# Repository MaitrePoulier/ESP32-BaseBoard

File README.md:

The goals of this BaseBoard:
* Support Bluetooth legacy for receiving audio from an external audio source
* Support 2x 18650 LiFePo4 cell that can be charged with the USB connector
* Low noise +/- 12.4V going to the mezzanine to powered Audio op-amp
* I2S port going to the mezz
* Support of the MHS 4.0 screen (ST7796S) with touch (XPT2046)
* can be placed inside an Pelican 1040 Micro Case

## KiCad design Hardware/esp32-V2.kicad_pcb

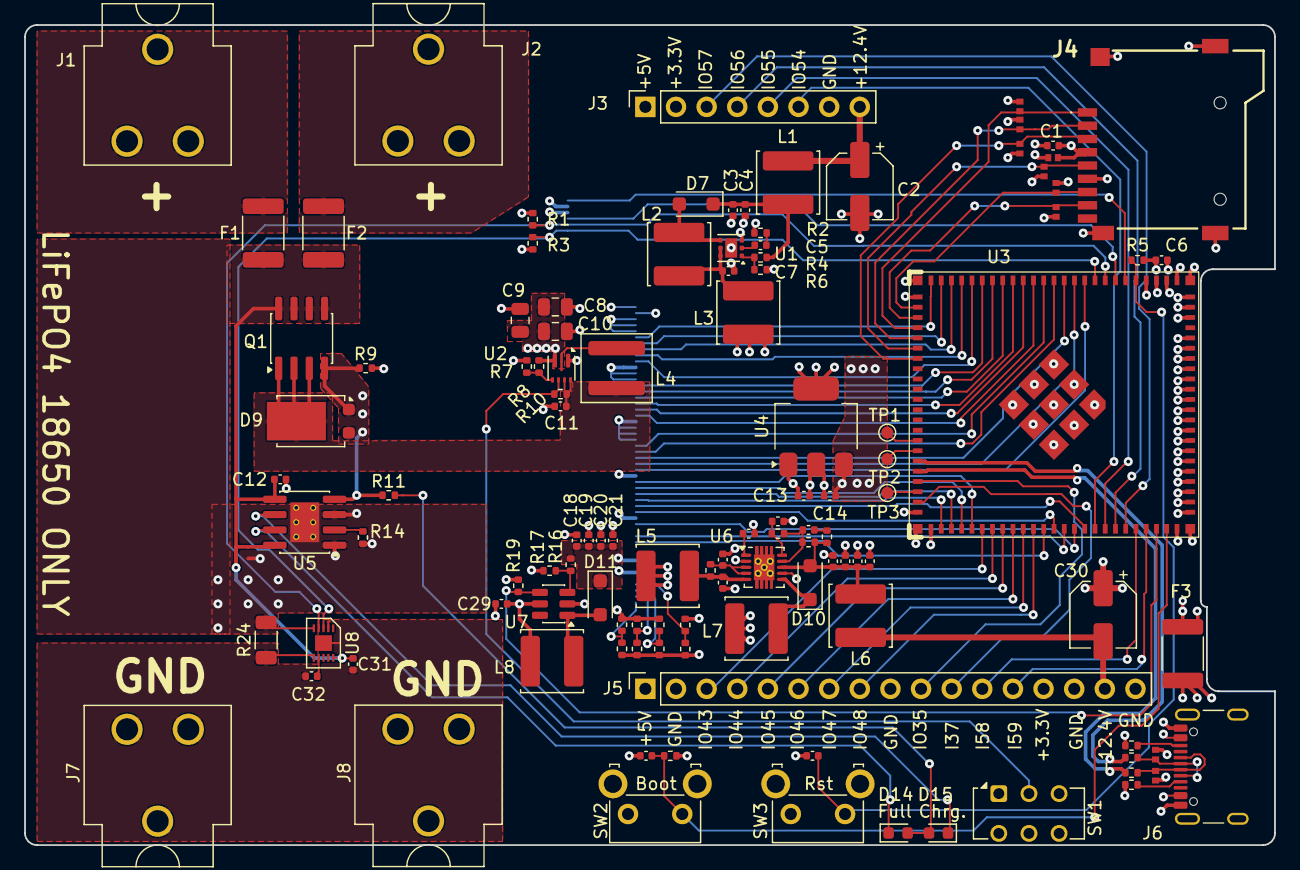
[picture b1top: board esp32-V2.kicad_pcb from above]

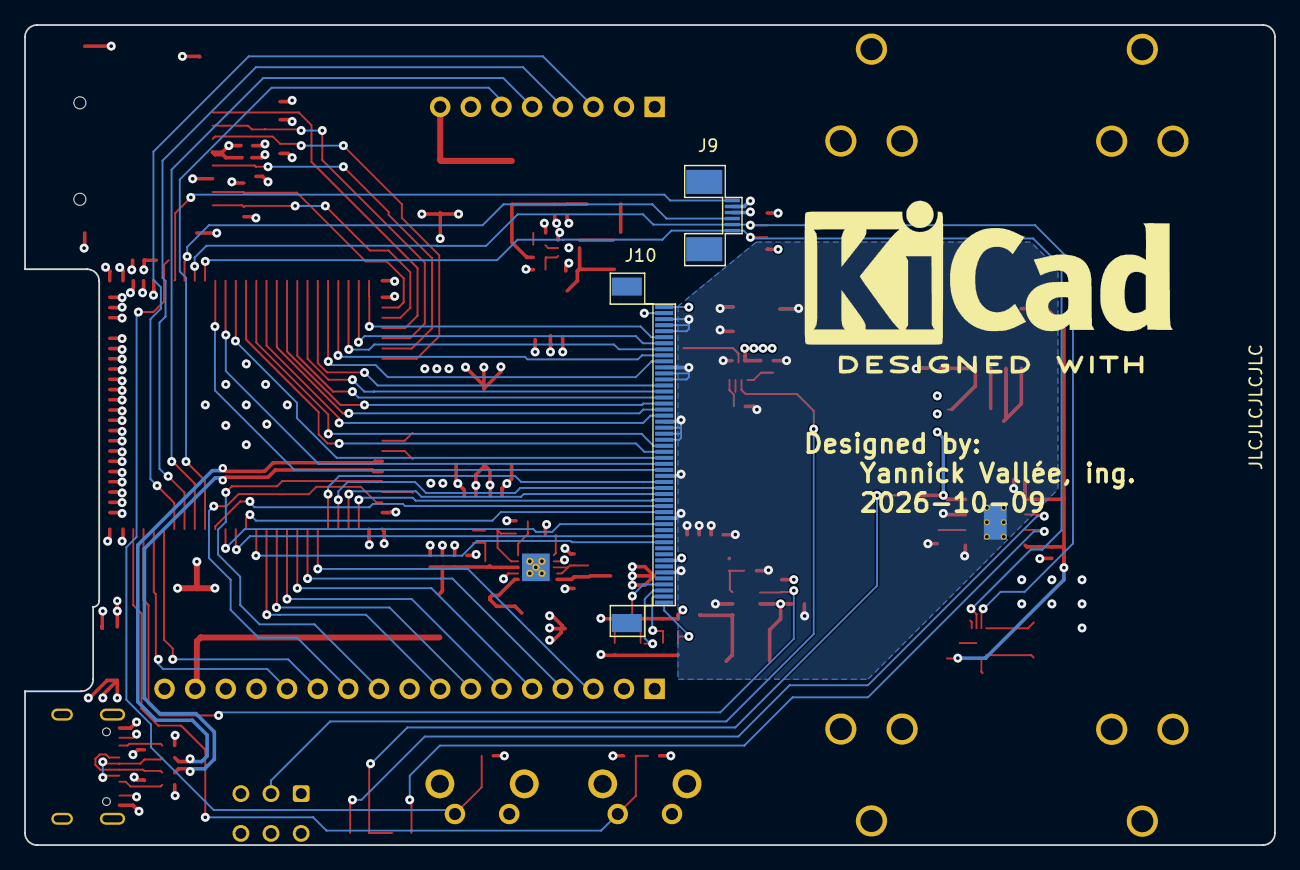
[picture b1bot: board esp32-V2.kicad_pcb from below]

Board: 4 copper layers, 103.7 x 68.0 mm, 118 parts (2 on the bottom side), 103 nets.

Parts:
C1, C6, C7, C11, C12, C13, C14, C28, C29: 10uF; C_0402_1005Metric
C2, C30: 22uF; CP_Elec_5x5.9
C3, C18, C19, C20, C21, C24, C25, C26, C27: 4.7uF; C_0402_1005Metric
C4, C5, C17: 4.7nF; C_0402_1005Metric
C8, C9, C10: 22uF; C_0805_2012Metric
C15, C23: 220nF; C_0402_1005Metric
C16: 10pF; C_0402_1005Metric
C31, C32: 470nF; C_0402_1005Metric
C33, C34: 1nF; C_0402_1005Metric
D1, D2, D3, D4, D5, D6, D8, D12, D13: BSDFN2C031U; D_DFN1006-2L
D7, D10, D11: Diode-DK24; D_SOD-123F
D9: Diode-PDS760; TO-277B
D14: Blue 2.9V; LED_0603_1608Metric
D15: Green, 3.2V; LED_0603_1608Metric
F1, F2, F3: BSMD1812-300-16V; Fuse_1812_4532Metric_Pad1.30x3.40mm_HandSolder
J1, J2, J7, J8: Conn_01x01_Socket; BatteryClip_Keystone_54_D16-19mm
J3: Conn_01x08_F_Header; PinSocket_1x08_P2.54mm_Vertical
J4: MSD-4-A; MSD4A
J5: PM254-1-17-Z-8.5; PinSocket_1x17_P2.54mm_Vertical
J6: USB_C_Receptacle-16p; USB_C_Receptacle_GCT_USB4105-xx-A_16P_TopMnt_Horizontal
J9: KH-FG0.5-H2.0-6PIN; ER-CON06HT-1
J10: HC-FPC-0.5-50P-FHH20
L1, L3, L5, L6: 2.9Ohms @ 1Mhz; L_Chilisin_BWVS00505030
L2, L7, L8: 10uH; L_Chilisin_BWVS00505030
L4: 1uH; L_Coilcraft_XAL5030-XXX
NT1: NetTie_2; NetTie-2_SMD_Pad0.16mm
Q1: DMP3015LSS-13; SOIC-8_3.9x4.9mm_P1.27mm
R1, R3, R5, R7, R9, R10, R13, R19, R20, R21, R22, R23, R25, R26, R27, R28, R30: 100k; R_0402_1005Metric
R2, R6: 10k; R_0402_1005Metric
R4: 91k; R_0402_1005Metric
R8, R16: 732k; R_0402_1005Metric
R11: 357Ω; R_0402_1005Metric
R12: 150k; R_0402_1005Metric
R14: 1.18k; R_0402_1005Metric
R15: 1.54M; R_0402_1005Metric
R17: 31.6k; R_0402_1005Metric
R18: 10Ω; R_0402_1005Metric
R24: 10mΩ; R_1206_3216Metric
R29, R33: 5.1k; R_0402_1005Metric
R31, R32: 47Ω; R_0402_1005Metric
SW1: SW_Push_DPDT; SW_CK_JS202011AQN_DPDT_Angled
SW2, SW3: SW-000001; SW_SPST_Omron_B3F-315x_Angled
TP1, TP2, TP3: TestPoint; TestPoint_Pad_D1.0mm
U1: TPS61170DRVR; WSON-6-1EP_2x2mm_P0.65mm_EP1x1.6mm
U2: IC-TPS61022; Texas_RWU0007A_VQFN-7_2x2mm_P0.5mm
U3: ESP32-S31-WROOM-3-N16R16V; ESP32-S31-WROOM-3
U4: LT1963AEST-3.3#TRPBF; SOT-223-3_TabPin2
U5: CN3158; SOIC-8-1EP_3.9x4.9mm_P1.27mm_EP2.41x3.3mm_ThermalVias-0p3mm
U6: TPS63700; Texas_S-PWSON-N10_ThermalVias
U7: MT3608; SOT-23-6
U8: MAX17055ETB+T; TDFN-10-EP-2x2p5-0p4mm

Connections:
+3.3V: C1.1, C6.1, C14.1, D4.2 (A2), J3.2, J4.4 (VDD), J5.14, J9.2, J10.1, J10.2, R1.1, R3.1, R5.1, R19.1, R20.2, R21.2, R22.2, R23.2, R30.1, U3.3 (3V3), U3.4 (3V3), U4.3 (OUT)
+5V: C8.1, C9.1, C10.1, C13.1, C29.1, J3.1, J5.1, L3.1, L5.1, L8.1, R8.2, U2.3 (VOUT), U4.1 (IN), U7.5 (IN)
+12.4V: C2.1, J3.8, L1.2
+14.5V: C18.1, C19.1, C20.1, C21.1, D11.1 (K), J10.43, R16.2
-12.4V: C30.2, J5.16, L6.2
/DC-DC/BACKLIGHTen: R19.2, U3.70 (GPIO60), U7.4 (EN)
/ESP32-S31/CLK: D5.2 (A2), J4.5 (CLK), U3.31 (SDIO_CLK/GPIO24)
/ESP32-S31/CMD: D3.2 (A2), J4.3 (CMD), U3.32 (SDIO_CMD/GPIO25)
/ESP32-S31/CS: J10.35, U3.60 (GPIO50/ADC2_CH0_N)
/ESP32-S31/DATA0: D6.2 (A2), J4.7 (DAT0), U3.27 (SDIO_DATA0/GPIO20)
/ESP32-S31/DATA1: D8.2 (A2), J4.8 (DAT1), U3.28 (SDIO_DATA1/GPIO21)
/ESP32-S31/DATA2: D1.2 (A2), J4.1 (DAT2), U3.29 (SDIO_DATA2/GPIO22)
/ESP32-S31/DATA3: D2.2 (A2), J4.2 (DAT3/CD), U3.30 (SDIO_DATA3/GPIO23)
/ESP32-S31/DE: J10.33, U3.49 (GPIO38)
/ESP32-S31/DS0: J10.28, U3.10 (GPIO4)
/ESP32-S31/DS1: J10.27, U3.11 (GPIO5)
/ESP32-S31/DS2: J10.26, U3.12 (GPIO6)
/ESP32-S31/DS3: J10.25, U3.13 (GPIO7)
/ESP32-S31/DS4: J10.24, U3.14 (GPIO8)
/ESP32-S31/DS8: J10.19, U3.15 (GPIO9)
/ESP32-S31/DS9: J10.18, U3.16 (GPIO10)
/ESP32-S31/DS10: J10.17, U3.17 (GPIO11)
/ESP32-S31/DS11: J10.16, U3.18 (GPIO12)
/ESP32-S31/DS12: J10.15, U3.19 (GPIO13)
/ESP32-S31/DS13: J10.14, U3.20 (GPIO14)
/ESP32-S31/DS16: J10.10, U3.21 (GPIO15)
/ESP32-S31/DS17: J10.9, U3.22 (GPIO16)
/ESP32-S31/DS18: J10.8, U3.23 (GPIO17)
/ESP32-S31/DS19: J10.7, U3.24 (GPIO18)
/ESP32-S31/DS20: J10.6, U3.25 (GPIO19)
/ESP32-S31/HS: J10.31, U3.51 (GPIO40)
/ESP32-S31/I2C1-SCL: J9.6, R3.2, U3.9 (GPIO1/XTAL_32K_P), U8.3 (SCL)
/ESP32-S31/I2C1-SDA: J9.5, R1.2, U3.8 (GPIO0/XTAL_32K_N), U8.4 (SDA)
/ESP32-S31/PCLK: J10.30, U3.52 (GPIO42/ADC1_CH0_N)
/ESP32-S31/RST: J10.40, U3.59 (GPIO49/ADC1_CH3_P)
/ESP32-S31/SCL: J10.37, U3.62 (GPIO52/ADC2_CH1_N)
/ESP32-S31/SD0: J10.34, U3.63 (GPIO53/ADC2_CH1_P)
/ESP32-S31/SDA: J10.39, U3.61 (GPIO51/ADC2_CH0_P)
/ESP32-S31/Touch-INT: J9.4, U3.7 (GPIO3)
/ESP32-S31/Touch-RST: J9.1, U3.6 (GPIO2)
/ESP32-S31/USB_D+: R32.2, U3.43 (GPIO34)
/ESP32-S31/USB_D-: R31.2, U3.42 (GPIO33)
/ESP32-S31/VS: J10.32, U3.50 (GPIO39)
/Screen/IM0: J10.50, R20.1, R25.2
/Screen/IM1: J10.49, R21.1, R26.2
/Screen/IM2: J10.48, R22.1, R27.2
/Screen/IM3: J10.47, R23.1, R28.2
/USB and Cells/D+: D13.2 (A2), J6.A6 (D+), J6.B6 (D+), R32.1
/USB and Cells/D-: D12.2 (A2), J6.A7 (D-), J6.B7 (D-), R31.1
/USB and Cells/Vin: C11.1, D9.3 (K), L4.1, Q1.1 (S), Q1.2 (S), Q1.3 (S), R10.1, U2.6 (MODE), U2.7 (VIN)
BOOT: C33.1, R30.2, SW2.1, U3.71 (GPIO61)
EN: C34.1, R5.2, SW3.1, U3.5 (EN)
GND: C1.2, C2.2, C3.2, C4.2, C6.2, C7.2, C8.2, C9.2, C10.2, C11.2, C12.2, C13.2, C14.2, C15.1, C17.2, C18.2, C19.2, C20.2, C21.2, C23.1, C24.2, C25.2, C26.2, C27.2, C28.2, C29.2, C30.1, C33.2, C34.2, D1.1 (A1), D2.1 (A1), D3.1 (A1), D4.1 (A1), D5.1 (A1), D6.1 (A1), D8.1 (A1), D12.1 (A1), D13.1 (A1), J3.7, J4.6 (VSS), J4.G1 (GND), J4.G2 (GND), J4.G3 (GND), J4.G4 (GND), J5.2, J5.9, J5.15, J5.17, J6.A1 (GND), J6.A12 (GND), J6.B1 (GND), J6.B12 (GND), J6.SH (SHIELD), J9.3, J10.3, J10.4, J10.5, J10.11, J10.12, J10.13, J10.20, J10.21, J10.22, J10.23, J10.29, J10.36, J10.45, L7.1, R2.1, R6.1, R7.1, R9.2, R14.1, R17.2, R24.2, R25.1, R26.1, R27.1, R28.1, R29.2, R33.2, SW1.3 (C), SW2.2, SW3.2, U1.3 (GND), U1.7 (TP), U2.1 (GND), U3.1 (GND), U3.2 (GND), U3.26 (GND), U3.47 (GND), U3.48 (GND), U3.72 (GND), U3.73 (GND), U3.74 (GND), U3.75 (GND), U3.76 (GND), U3.77 (GND), U3.78 (GND), U3.79 (GND), U3.80 (GND), U3.81 (GND), U3.82 (GND), U3.83 (GND), U3.84 (GND), U3.85 (GND), U3.86 (GND), U3.87 (GND), U3.88 (GND), U3.89 (GND), U3.90 (GND), U3.92 (GND), U3.93 (GND), U3.94 (GND), U3.95 (GND), U3.96 (GND), U3.97 (GND), U3.98 (GND), U3.99 (GND), U4.2 (GND), U5.1 (TEMP), U5.3 (GND), U5.9 (GND), U6.2 (GND), U6.7 (PS_GND), U6.11 (TP), U7.2 (GND), U8.5 (CSn)
GNDREF: C31.1, C32.1, J7.1 (Pin_1_1), J8.1 (Pin_1_1), NT1.1, R24.1, U8.2 (AIN), U8.11 (EP)
IO35: J5.10, U3.44 (GPIO35)
IO37: J5.11, U3.46 (GPIO37)
IO43: J5.3, U3.53 (GPIO43/ADC1_CH0_P)
IO44: J5.4, U3.54 (GPIO44/ADC1_CH1_N)
IO45: J5.5, U3.55 (GPIO45/ADC1_CH1_P)
IO46: J5.6, U3.56 (GPIO46/ADC1_CH2_N)
IO47: J5.7, U3.57 (GPIO47/ADC1_CH2_P)
IO48: J5.8, U3.58 (GPIO48/ADC1_CH3_N)
IO54: J3.6, U3.64 (MTDO/GPIO54)
IO55: J3.5, U3.65 (MTCK/GPIO55)
IO56: J3.4, U3.66 (MTDI/GPIO56)
IO57: J3.3, U3.67 (MTMS/GPIO57)
IO58-UART0-TX: J5.12, U3.68 (UART0_TXD/GPIO58)
IO59-UART0-RX: J5.13, U3.69 (UART0_RXD/GPIO59)
unnamed: C5.2, R2.2
unnamed: C16.2, R13.2
unnamed: D7.2 (A), L2.2, U1.4 (SW)
unnamed: C3.1, C4.1, D7.1 (K), L1.1, R4.2
unnamed: C24.1, C25.1, C26.1, C27.1, D10.2 (A), L6.1, R13.1, R15.1, U6.8 (OUT)
unnamed: D10.1 (K), L7.2, U6.6 (SW)
unnamed: D11.2 (A), L8.2, U7.1 (SW)
unnamed: D14.2 (A), D15.2 (A), R11.2
unnamed: D14.1 (K), U5.7 (~CHRG)
unnamed: D15.1 (K), U5.6 (~DONE)
unnamed: F3.1, J6.A4 (VBUS), J6.A9 (VBUS), J6.B4 (VBUS), J6.B9 (VBUS)
unnamed: F1.2, J1.1 (Pin_1_1)
unnamed: F2.2, J2.1 (Pin_1_1)
unnamed: J6.A5 (CC1), R33.1
unnamed: J6.B5 (CC2), R29.1
unnamed: C5.1, U1.2 (COMP)
unnamed: C7.1, L2.1, L3.2, U1.5 (CTRL), U1.6 (VIN)
unnamed: R4.1, R6.2, U1.1 (FB)
unnamed: R10.2, SW1.2 (B), U2.5 (EN)
unnamed: R7.2, R8.1, U2.4 (FB)
unnamed: L4.2, U2.2 (SW)
unnamed: TP3.1 (1_1), U3.45 (GPIO36*)
unnamed: TP2.1 (1_1), U3.41 (USB_DM)
unnamed: TP1.1 (1_1), U3.40 (USB_DP)
unnamed: R14.2, U5.2 (ISET)
unnamed: C17.1, U6.1 (COMP)
unnamed: C23.2, R18.1, U6.3 (VIN), U6.4 (EN)
unnamed: C16.1, R12.1, R15.2, U6.9 (FB)
unnamed: C28.1, L5.2, R18.2, U6.5 (IN)
unnamed: C15.2, R12.2, U6.10 (VREF)
unnamed: R16.1, R17.1, U7.3 (FB)
unnamed: NT1.2, U8.6 (CSp)
unnamed: C32.2, U8.7 (REG)
V-USB: D9.1 (A), D9.2 (A), F3.2, Q1.4 (G), R9.1, R11.1, U5.4 (VIN)
Vbatt: C12.1, C31.2, F1.1, F2.1, Q1.5 (D), Q1.6 (D), Q1.7 (D), Q1.8 (D), U5.5 (BAT), U5.8 (FB), U8.10 (BATT)

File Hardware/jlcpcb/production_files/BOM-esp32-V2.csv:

Comment,Designator,Footprint,LCSC,Quantity
1.18k,R14,R_0402_1005Metric,C2088001,1
1.54M,R15,R_0402_1005Metric,C407713,1
100k,"R1,R10,R19,R3,R30,R5,R9",R_0402_1005Metric,C25741,7
100k,"R13,R21,R25,R27,R28,R7",R_0402_1005Metric,C2909355,6
10k,"R2,R6",R_0402_1005Metric,C25744,2
10mï¿,R24,R_1206_3216Metric,C188070,1
10pF,C16,C_0402_1005Metric,C513681,1
10uF,"C1,C11,C12,C13,C14,C28,C29,C6,C7",C_0402_1005Metric,C20069813,9
10uH,"L2,L7,L8",L_Chilisin_BWVS00505030,C520336,3
10ï¿,R18,R_0402_1005Metric,C2906862,1
150k,R12,R_0402_1005Metric,C2909320,1
1nF,"C33,C34",C_0402_1005Metric,C2167623,2
1uH,L4,L_Coilcraft_XAL5030-XXX,C18208905,1
2.9Ohms @ 1Mhz,"L1,L3,L5,L6",L_Chilisin_BWVS00505030,C711211,4
220nF,"C15,C23",C_0402_1005Metric,C915854,2
22uF,"C10,C8,C9",C_0805_2012Metric,C23692981,3
22uF,"C2,C30",CP_Elec_5x5.9,C454605,2
31.6k,R17,R_0402_1005Metric,C852720,1
357ï¿,R11,R_0402_1005Metric,C852736,1
4.7nF,"C17,C4,C5",C_0402_1005Metric,C1518204,3
4.7uF,"C18,C19,C20,C21,C24,C25,C26,C27,C3",C_0402_1005Metric,C6119795,9
470nF,"C31,C32",C_0402_1005Metric,C471404,2
47ï¿,"R31,R32",R_0402_1005Metric,C2909362,2
5.1k,"R29,R33",R_0402_1005Metric,C5356293,2
732k,"R16,R8",R_0402_1005Metric,C27016,2
91k,R4,R_0402_1005Metric,C2909393,1
BSDFN2C031U,"D1,D12,D13,D2,D3,D4,D5,D6,D8",D_DFN1006-2L,C600818,9
BSMD1812-300-16V,"F1,F2,F3",Fuse_1812_4532Metric_Pad1.30x3.40mm_HandSolder,C883162,3
Blue 2.9V,D14,LED_0603_1608Metric,C51933294,1
CN3158,U5,SOIC-8-1EP_3.9x4.9mm_P1.27mm_EP2.41x3.3mm_ThermalVias-0p3mm,C559032,1
DMP3015LSS-13,Q1,SOIC-8_3.9x4.9mm_P1.27mm,C508208,1
Diode-DK24,"D10,D11,D7",D_SOD-123F,C22466352,3
Diode-PDS760,D9,TO-277B,C3018534,1
ESP32-S31-WROOM-3-N16R16V,U3,ESP32-S31-WROOM-3,C55371223,1
"Green, 3.2V",D15,LED_0603_1608Metric,C51933293,1
HC-FPC-0.5-50P-FHH20,J10,HC-FPC-0.5-50P-FHH20,C19273943,1
IC-TPS61022,U2,Texas_RWU0007A_VQFN-7_2x2mm_P0.5mm,C915088,1
KH-FG0.5-H2.0-6PIN,J9,ER-CON06HT-1,C709363,1
LT1963AEST-3.3#TRPBF,U4,SOT-223-3_TabPin2,C459918,1
MAX17055ETB+T,U8,TDFN-10-EP-2x2p5-0p4mm,C2976422,1
MSD-4-A,J4,MSD4A,C22367949,1
MT3608,U7,SOT-23-6,C84817,1
SW-000001,"SW2,SW3",SW_SPST_Omron_B3F-315x_Angled,C397284,2
SW_Push_DPDT,SW1,SW_CK_JS202011AQN_DPDT_Angled,C221662,1
TPS61170DRVR,U1,WSON-6-1EP_2x2mm_P0.65mm_EP1x1.6mm,C15163,1
TPS63700,U6,Texas_S-PWSON-N10_ThermalVias,C54792,1
USB_C_Receptacle-16p,J6,USB_C_Receptacle_GCT_USB4105-xx-A_16P_TopMnt_Horizontal,C3025063,1

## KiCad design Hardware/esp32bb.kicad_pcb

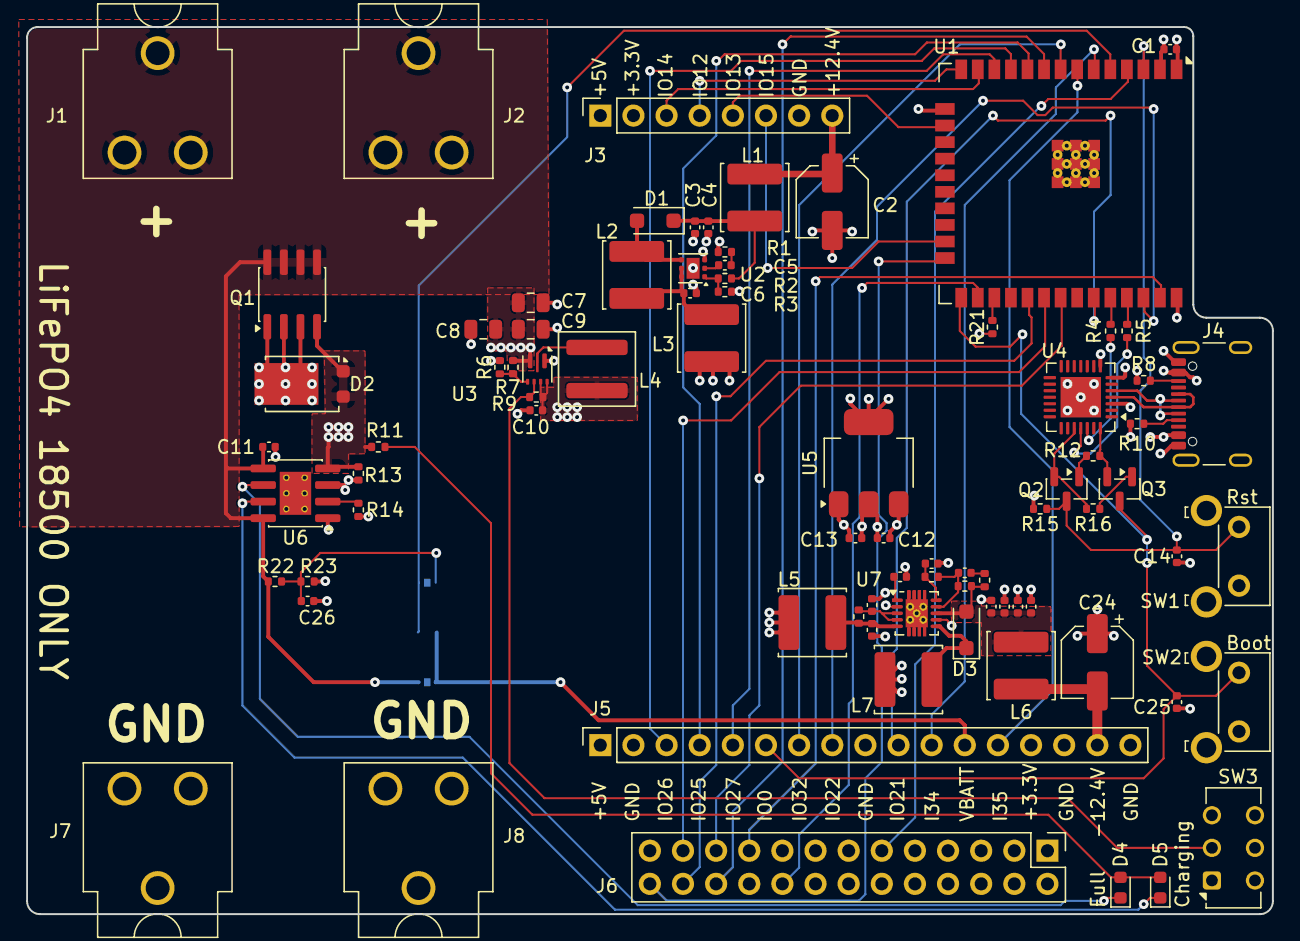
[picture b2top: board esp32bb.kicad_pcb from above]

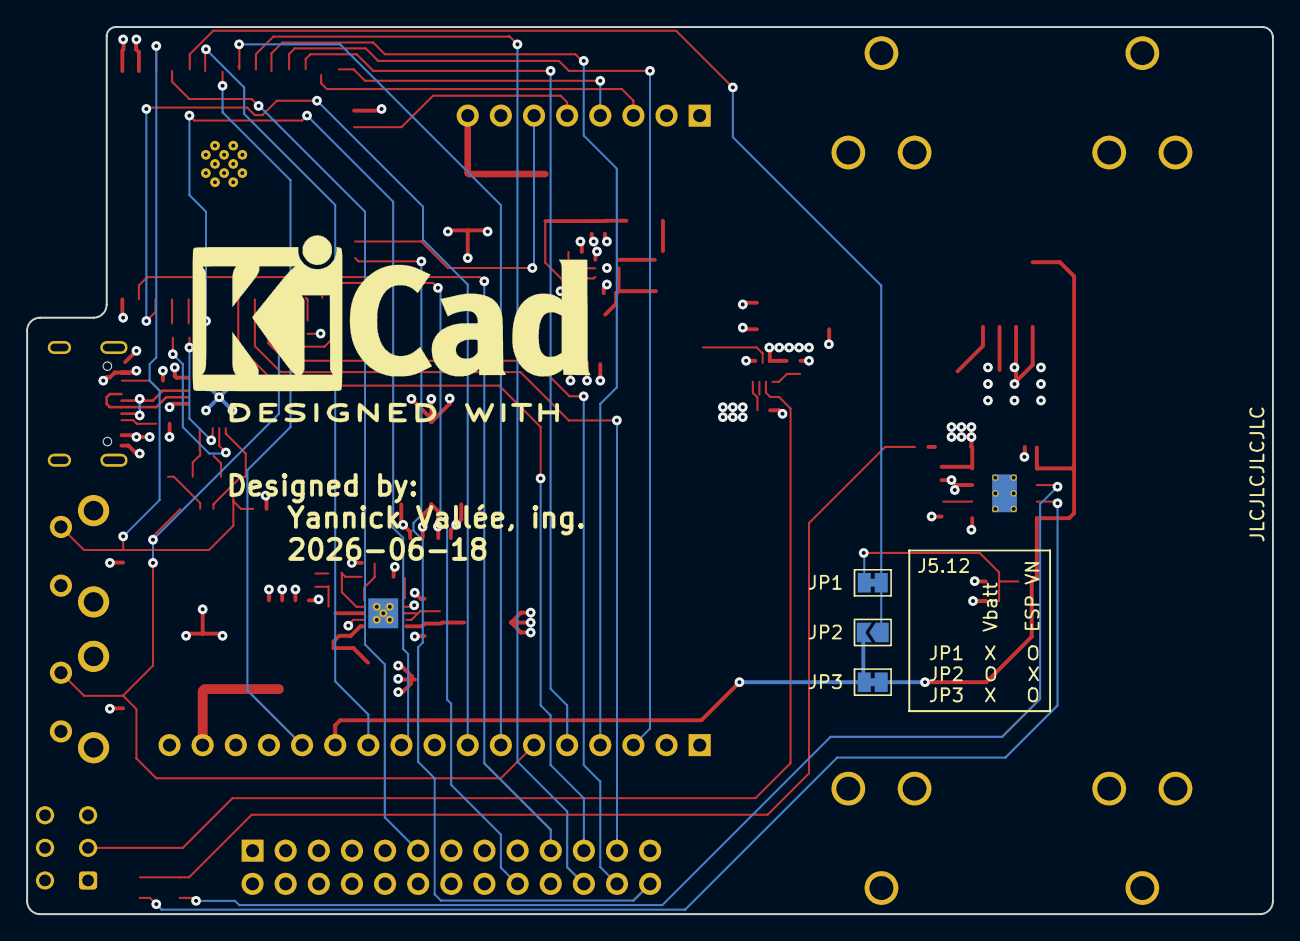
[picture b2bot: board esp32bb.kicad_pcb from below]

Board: 4 copper layers, 95.5 x 68.0 mm, 85 parts (3 on the bottom side), 67 nets.

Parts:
C1, C6, C10, C11, C12, C13, C23: 10uF; C_0402_1005Metric
C2, C24: 22uF; CP_Elec_5x5.9
C3, C19, C20, C21, C22: 4.7uF; C_0402_1005Metric
C4, C5, C17, C26: 4.7nF; C_0402_1005Metric
C7, C8, C9: 22uF; C_0805_2012Metric
C14, C25: 1nF; C_0402_1005Metric
C15, C18: 220nF; C_0402_1005Metric
C16: 10pF; C_0402_1005Metric
D1, D3: D_Schottky; D_SOD-123F
D2: Fuxinsemi_PDS760; TO-277B
D4: Green, 3.2V; LED_0603_1608Metric
D5: Blue 2.9V; LED_0603_1608Metric
J1, J2, J7, J8: Conn_01x01_Socket; BatteryClip_Keystone_54_D16-19mm
J3: Conn_01x08; PinSocket_1x08_P2.54mm_Vertical
J4: USB_C_Receptacle_USB2.0_16P; USB_C_Receptacle_GCT_USB4105-xx-A_16P_TopMnt_Horizontal
J5: PM254-1-17-Z-8.5; PinSocket_1x17_P2.54mm_Vertical
J6: Conn_02x13_Odd_Even; PinHeader_2x13_P2.54mm_Vertical
JP1, JP3: SolderJumper_2_Bridged; SolderJumper-2_P1.3mm_Bridged_Pad1.0x1.5mm
JP2: SolderJumper_2_Open; SolderJumper-2_P1.3mm_Open_TrianglePad1.0x1.5mm
L1, L3, L5, L6: 2.9Ohms @ 1Mhz; L_Chilisin_BWVS00505030
L2, L7: 10uH; L_Chilisin_BWVS00505030
L4: 1uH; L_Coilcraft_XAL5030-XXX
Q1: DMP3015LSS-13; SOIC-8_3.9x4.9mm_P1.27mm
Q2, Q3: MMBT3904; SOT-23
R1, R3, R12, R15, R16, R21: 10k; R_0402_1005Metric
R2: 91k; R_0402_1005Metric
R4, R5: 100; R_0402_1005Metric
R6, R9, R13, R18: 100k; R_0402_1005Metric
R7, R22, R23: 732k; R_0402_1005Metric
R8, R10: 5.1k; R_0402_1005Metric
R11: 180; R_0402_1005Metric
R14: 1.18k; R_0402_1005Metric
R17: 150k; R_0402_1005Metric
R19: 1.54M; R_0402_1005Metric
R20: 10Ω; R_0402_1005Metric
SW1, SW2: SW_Push; SW_SPST_Omron_B3F-315x_Angled
SW3: SW_Push_DPDT; SW_CK_JS202011AQN_DPDT_Angled
U1: ESP32-WROOM-32E-N8R2; ESP32-WROOM-32E-0p3mm
U2: TPS61170DRVR; WSON-6-1EP_2x2mm_P0.65mm_EP1x1.6mm
U3: TPS61022; Texas_RWU0007A_VQFN-7_2x2mm_P0.5mm
U4: CP2102; QFN-28-1EP_5x5mm_P0.5mm_EP3.1x3.1mm
U5: LT1963AEST-3.3#TRPBF; SOT-223-3_TabPin2
U6: CN3158; SOIC-8-1EP_3.9x4.9mm_P1.27mm_EP2.41x3.3mm_ThermalVias-0p3mm
U7: TPS63700; Texas_S-PWSON-N10_ThermalVias

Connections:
+3.3V: C1.1, C12.1, J3.2, J5.14, J6.1, J6.17, R15.2, R21.1, U1.2 (3V3), U5.3 (OUT)
+5V: C7.1, C8.1, C9.1, C13.1, J3.1, J5.1, J6.2, J6.4, L3.1, L5.1, R7.2, U3.3 (VOUT), U4.7 (REGIN), U4.8 (VBUS), U5.1 (IN)
+12.4V: C2.1, J3.8, L1.2
-12.4V: C24.2, J5.16, L6.2
/Power/Vin: C10.1, D2.3 (K), L4.1, Q1.1 (S), Q1.2 (S), Q1.3 (S), R9.1, U3.6 (MODE), U3.7 (VIN)
Batt-Monitor: JP1.2 (B), JP2.1 (A), U1.5 (SENSOR_VN)
D+: J4.A6 (D+), J4.B6 (D+), U4.4 (D+)
D-: J4.A7 (D-), J4.B7 (D-), U4.5 (D-)
DTR: Q3.2 (E), R12.2, U4.28 (DTR)
EN: C14.1, Q2.3 (C), R15.1, SW1.1, U1.3 (EN)
GND: C1.2, C2.2, C3.2, C4.2, C6.2, C7.2, C8.2, C9.2, C10.2, C11.2, C12.2, C13.2, C14.2, C15.1, C17.2, C18.1, C19.2, C20.2, C21.2, C22.2, C23.2, C24.1, C25.2, C26.2, J3.7, J4.A1 (GND), J4.A12 (GND), J4.B1 (GND), J4.B12 (GND), J4.SH (SHIELD), J5.2, J5.9, J5.15, J5.17, J6.6, J6.9, J6.14, J6.20, J6.25, J7.1 (Pin_1_1), J8.1 (Pin_1_1), L7.1, R1.1, R3.1, R6.1, R8.2, R10.2, R13.2, R14.1, R23.1, SW1.2, SW2.2, SW3.3 (C), U1.1 (GND), U1.15 (GND), U1.38 (GND), U1.39 (GND-PAD), U2.3 (GND), U2.7 (TP), U3.1 (GND), U4.3 (GND), U4.29 (GND), U5.2 (GND), U6.1 (TEMP), U6.3 (GND), U6.9 (GND), U7.2 (GND), U7.7 (PS_GND), U7.11 (TP)
I34: J5.11, U1.6 (IO34)
I35: J5.13, U1.7 (IO35)
IO0(boot): C25.1, J5.6, Q3.3 (C), SW2.1, U1.25 (IO0)
IO12: J3.4, U1.14 (IO12)
IO13: J3.5, U1.16 (IO13)
IO14: J3.3, U1.13 (IO14)
IO15: J3.6, U1.23 (IO15)
IO21: J5.10, U1.33 (IO21)
IO22: J5.8, U1.36 (IO22)
IO25: J5.4, U1.10 (IO25)
IO26: J5.3, U1.11 (IO26)
IO27: J5.5, U1.12 (IO27)
IO32: J5.7, U1.8 (IO32)
LCD_CS: J6.24, U1.29 (IO5)
LCD_RS: J6.18, U1.26 (IO4)
LCD_RST: J6.22, U1.9 (IO33)
LCD/TP_CLK: J6.23, U1.30 (IO18)
LCD/TP_MISO: J6.21, U1.31 (IO19)
LCD/TP_MOSI: J6.19, U1.37 (IO23)
unnamed: C5.2, R1.2
unnamed: C16.2, R18.2
unnamed: D1.2 (A), L2.2, U2.4 (SW)
unnamed: C3.1, C4.1, D1.1 (K), L1.1, R2.2
unnamed: C19.1, C20.1, C21.1, C22.1, D3.2 (A), L6.1, R18.1, R19.1, U7.8 (OUT)
unnamed: D3.1 (K), L7.2, U7.6 (SW)
unnamed: D4.2 (A), D5.2 (A), R11.1
unnamed: D4.1 (K), U6.6 (~DONE)
unnamed: D5.1 (K), U6.7 (~CHRG)
unnamed: J4.A5 (CC1), R10.1
unnamed: J4.B5 (CC2), R8.1
unnamed: C26.1, JP1.1 (A), R22.1, R23.2
unnamed: Q2.1 (B), R12.1
unnamed: Q3.1 (B), R16.1
unnamed: R21.2, U1.27 (IO16)
unnamed: C5.1, U2.2 (COMP)
unnamed: C6.1, L2.1, L3.2, U2.5 (CTRL), U2.6 (VIN)
unnamed: R2.1, R3.2, U2.1 (FB)
unnamed: R9.2, SW3.2 (B), U3.5 (EN)
unnamed: R6.2, R7.1, U3.4 (FB)
unnamed: L4.2, U3.2 (SW)
unnamed: R5.1, U4.25 (RXD)
unnamed: R4.1, U4.26 (TXD)
unnamed: R14.2, U6.2 (ISET)
unnamed: C17.1, U7.1 (COMP)
unnamed: C18.2, R20.1, U7.3 (VIN), U7.4 (EN)
unnamed: C16.1, R17.1, R19.2, U7.9 (FB)
unnamed: C23.1, L5.2, R20.2, U7.5 (IN)
unnamed: C15.2, R17.2, U7.10 (VREF)
RTS: Q2.2 (E), R16.2, U4.24 (RTS)
RXDtoTXD0: R5.2, U1.35 (TXD0)
TP_CS: J6.26, U1.24 (IO2)
TP_IRQ: J6.11, U1.4 (SENSOR_VP)
TXDtoRXD0: R4.2, U1.34 (RXD0)
V-USB: D2.1 (A), D2.2 (A), J4.A4 (VBUS), J4.A9 (VBUS), J4.B4 (VBUS), J4.B9 (VBUS), Q1.4 (G), R11.2, R13.1, U6.4 (VIN)
Vbatt: C11.1, J1.1 (Pin_1_1), J2.1 (Pin_1_1), JP3.1 (A), Q1.5 (D), Q1.6 (D), Q1.7 (D), Q1.8 (D), R22.2, U6.5 (BAT), U6.8 (FB)
Vbatt-VN: J5.12, JP2.2 (B), JP3.2 (B)

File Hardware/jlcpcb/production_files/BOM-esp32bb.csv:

Comment,Designator,Footprint,LCSC,Quantity
1.18k,R14,R_0402_1005Metric,C2088001,1
1.54M,R19,R_0402_1005Metric,C407713,1
100,"R4,R5",R_0402_1005Metric,C25076,2
100k,"R13,R9",R_0402_1005Metric,C25741,2
100k,"R18,R6",R_0402_1005Metric,C2909355,2
10k,"R1,R12,R15,R16,R21,R3",R_0402_1005Metric,C25744,6
10pF,C16,C_0402_1005Metric,C513681,1
10uF,"C1,C10,C11,C12,C13,C23,C6",C_0402_1005Metric,C20069813,7
10uH,"L2,L7",L_Chilisin_BWVS00505030,C144391,2
10Ω,R20,R_0402_1005Metric,C2906862,1
150k,R17,R_0402_1005Metric,C2909320,1
180,R11,R_0402_1005Metric,C5141075,1
1nF,"C14,C25",C_0402_1005Metric,C2167623,2
1uH,L4,L_Coilcraft_XAL5030-XXX,C18208905,1
2.9Ohms @ 1Mhz,"L1,L3,L5,L6",L_Chilisin_BWVS00505030,C711211,4
220nF,"C15,C18",C_0402_1005Metric,C915854,2
22uF,"C7,C8,C9",C_0805_2012Metric,C23692981,3
22uF,"C2,C24",CP_Elec_5x5.9,C454605,2
4.7nF,"C17,C26,C4,C5",C_0402_1005Metric,C1518204,4
4.7uF,"C19,C20,C21,C22,C3",C_0402_1005Metric,C6119795,5
5.1k,"R10,R8",R_0402_1005Metric,C5356293,2
732k,"R22,R23,R7",R_0402_1005Metric,C27016,3
91k,R2,R_0402_1005Metric,C2909393,1
Blue 2.9V,D5,LED_0603_1608Metric,C51933294,1
CN3158,U6,SOIC-8-1EP_3.9x4.9mm_P1.27mm_EP2.41x3.3mm_ThermalVias-0p3mm,C559032,1
CP2102,U4,QFN-28-1EP_5x5mm_P0.5mm_EP3.1x3.1mm,C964632,1
DMP3015LSS-13,Q1,SOIC-8_3.9x4.9mm_P1.27mm,C508208,1
D_Schottky,"D1,D3",D_SOD-123F,C22466352,2
ESP32-WROOM-32E-N8R2,U1,ESP32-WROOM-32E-0p3mm,C5361945,1
Fuxinsemi_PDS760,D2,TO-277B,C3018534,1
"Green, 3.2V",D4,LED_0603_1608Metric,C51933293,1
LT1963AEST-3.3#TRPBF,U5,SOT-223-3_TabPin2,C459918,1
MMBT3904,"Q2,Q3",SOT-23,C364310,2
TPS61022,U3,Texas_RWU0007A_VQFN-7_2x2mm_P0.5mm,C915088,1
TPS61170DRVR,U2,WSON-6-1EP_2x2mm_P0.65mm_EP1x1.6mm,C15163,1
TPS63700,U7,Texas_S-PWSON-N10_ThermalVias,C54792,1
USB_C_Receptacle_USB2.0_16P,J4,USB_C_Receptacle_GCT_USB4105-xx-A_16P_TopMnt_Horizontal,C3025063,1

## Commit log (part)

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2026-06-22 First commit.
2026-06-22 Clean up
2026-06-22 Adding VSCode workspace
2026-06-22 Good ESP32 base project
2026-06-22 Start
2026-06-22 Clean-up du projet pour qu'il fonctionne sur le ESP32 (et non le ESP32-S3)
2026-06-22 Add image of ESP32 BaseBoard to README
2026-06-22 Update README with BaseBoard goals and features
    Added goals and features of the BaseBoard to the README.
2026-06-24 Adding WRK-GBR and Design
2026-06-25 clean-up
2026-06-25 Adding TFT_espi initial configuration
